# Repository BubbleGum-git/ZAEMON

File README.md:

# BE Capstone Project

**ZAEMON — Dynamically Balanced Wheeled Bipedal Robot**  
[Our Project proposal presentation](https://www.youtube.com/watch?v=3FdDc5E4eX4)

---

## Team Details

| Sr. No. | Name of Student | Roll No. | Branch                  | Email ID |
| ------- | --------------- | -------- | ----------------------- | -------- |
| 1       |Suraj Kumbhar|9| Automation and Robotics |2023.suraj.kumbhar@ves.ac.in|
| 2       |Baljeet Singh Labana|10| Automation and Robotics |2023.baljeet.labana@ves.ac.in|
| 3       |Aayush Maluste|13| Automation and Robotics |2023.aayush.maulste@ves.ac.in|
| 4       |Jai Bagul|35| Automation and Robotics |2023.jai.bagul@ves.ac.in|

---

## Guide Details

**Project Guide:** 
Madhumati Khuspe  
**Department:** 
Automation and Robotics  
**Institute:** 
Vivekanand Education Society's Institute of Technology, Mumbai

---

## Problem Statement

Conventional wheeled robots provide efficient locomotion but are generally limited to stable configurations and relatively simple movements. Legged robots offer greater mobility and dynamic capabilities but require more complex mechanical structures and control systems.

The aim of ZAEMON is to design and develop an open source dynamically balanced wheeled bipedal robot platform and hardware capable of maintaining balance, performing controlled wheeled locomotion, and executing dynamic movements such as jumping through real-time sensing, trajectory planning, dynamic modelling, and feedback control.

---

## Abstract

ZAEMON is a dynamically balanced wheeled bipedal robot developed to combine the efficiency of wheeled locomotion with the dynamic capabilities of a legged robotic system. Due to its variable center of mass, the robot behaves similarly to an inverted pendulum and requires continuous active stabilization to remain balanced.

The project focuses on the mechanical design, kinematic and dynamic modelling and real-time control of the robot.

An IMU provides real-time orientation feedback for estimating the robot's tilt and motion. PID control is used for balance stabilization and normal locomotion, while computed torque control is investigated for dynamic movements such as jumping.

The project aims to develop and experimentally validate a compact robotic platform capable of dynamic balancing, controlled locomotion, and agile movement.

---

## Objectives

1. To design and develop a dynamically balanced wheeled bipedal robot.
2. To study the kinematics and dynamics of the robotic system.
3. To implement inverse dynamics.
4. To develop smooth joint-space and Cartesian-space trajectories.
5. To implement real-time balance control using IMU feedback.
6. To implement PID-based stabilization for balancing and locomotion.
7. To investigate computed torque control for dynamic movements.
8. To integrate the mechanical, electrical, and software systems.
9. To experimentally test and validate the developed system.

---

## Existing System

Conventional wheeled robots provide efficient and relatively simple locomotion but have limited ability to dynamically change their body configuration or perform agile movements.

Legged robots provide greater mobility and dynamic capabilities but typically involve:

* Higher mechanical complexity
* Multiple actuators
* Complex control algorithms
* Higher computational requirements
* Increased power consumption

ZAEMON explores a hybrid approach that combines efficient wheeled locomotion with actively controlled leg joints.

---

## Current Hardware

The hardware architecture consists of:

* Microcontroller ESP32 S3
* IMU MPU6050
* Motors and actuators - BLDC Gimbal Motor
* Motor drivers - DRV8313 FOC driver
* Encoders - AS5600 Magnetic encoder
* Power supply and battery system
* Voltage regulation and power distribution circuitry

Detailed hardware specifications will be documented as the design is finalized.

---

## Design Files

Design files are maintained in the following directories:

```text
hardware/
├── CAD/
```

---

## Circuit Diagram

The circuit diagram will be added as the electronics architecture is finalized.

---

### Control Algorithm

1. Initialize the controller and sensors.
2. Read IMU and encoder measurements.
3. Estimate the current robot state.
4. Calculate the error from the desired state.
5. Generate the desired trajectory.
6. Calculate the required control action.
7. Generate motor commands.
8. Apply commands to the actuators.
9. Read the updated sensor state.
10. Repeat the control loop in real time.

---

## Implementation Details

### Hardware Implementation

The hardware implementation consists of the mechanical structure, actuators, motor drivers, embedded controller, IMU, encoders, and power system.

The mechanical structure is designed to provide the required degrees of freedom for balancing, locomotion, and dynamic movement.

ime feedback

---

## Repository Structure

```text
ZAEMON/
│
├── README.md
│
├── docs/
│   ├── progress/
│   ├── design/
│   └── reports/
│
├── hardware/
│   ├── CAD/
│   ├── PCB/
│   ├── schematics/
│   └── BOM/
│
├── software/
│   ├── firmware/
│   ├── control/
│   ├── simulation/
│   └── tools/
│
├── images/
│
└── reference/
```

---

## How to Run

Build, firmware upload, and simulation instructions will be added as the software and hardware platforms are finalized.

---

## Applications

Potential applications of ZAEMON include:

1. Research in dynamically balanced robotics.
2. Agile robotic locomotion research.
3. Balance and control system research.
4. Dynamic trajectory and model-based control research.
5. Educational and experimental robotics.

---

## Advantages

1. Combines wheeled locomotion with bipedal movement.
2. Enables active dynamic balancing.
3. Supports model-based motion planning and control.
4. Provides a platform for studying dynamic robotic movement.
5. Can be extended with advanced control and autonomous capabilities.

---

## Limitations

1. Requires continuous active control for maintaining balance.
2. Dynamic movement requires accurate state estimation and modelling.
3. Mechanical and control complexity is higher than conventional wheeled robots.
4. Actuator and battery performance constrain the robot's capabilities.
5. Initial testing is intended for controlled environments.

---

## Future Scope

Future development may include:

* Autonomous navigation
* Advanced sensor fusion and state estimation
* Adaptive and robust control
* Improved landing and impact control
* More complex dynamic movements
* Real-time optimization of the dynamic model
* Improved mechanical and actuator design

---

## License

This project is developed as part of the BE Capstone Project at VESIT, Mumbai.

**For academic and research purposes.**

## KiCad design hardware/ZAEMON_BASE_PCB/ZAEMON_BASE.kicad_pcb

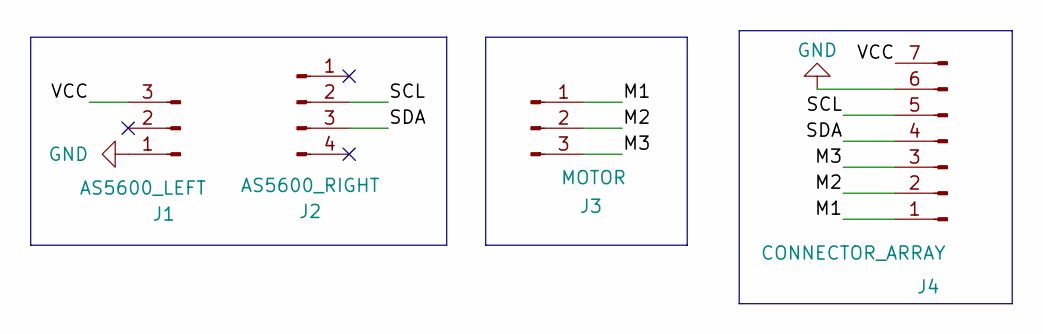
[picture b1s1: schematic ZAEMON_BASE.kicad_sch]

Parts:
J1: AS5600_LEFT; PinHeader_1x03_P2.54mm_Vertical
J2: AS5600_RIGHT; PinHeader_1x04_P2.54mm_Vertical
J3: MOTOR; PinHeader_1x03_P2.54mm_Vertical
J4: CONNECTOR_ARRAY; PinHeader_1x07_P2.54mm_Vertical

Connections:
/M1: J3.1, J4.1
/M2: J3.2, J4.2
/M3: J3.3, J4.3
/SCL: J2.2, J4.5
/SDA: J2.3, J4.4
/VCC: J1.3, J4.7
GND: J1.1, J4.6

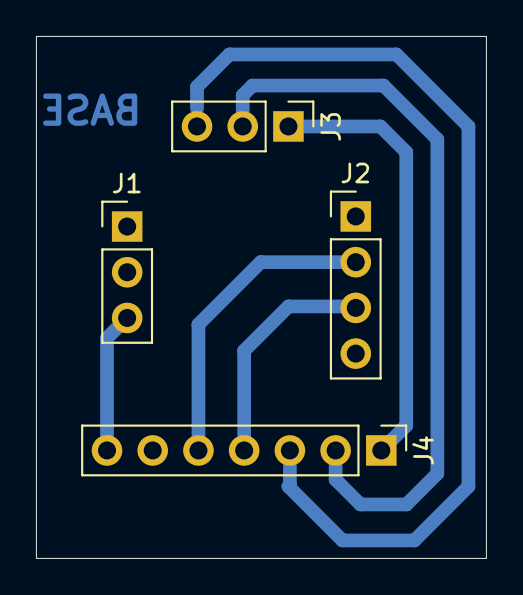
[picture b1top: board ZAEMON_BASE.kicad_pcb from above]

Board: 2 copper layers, 25.0 x 29.0 mm, 4 parts (0 on the bottom side), 7 nets.

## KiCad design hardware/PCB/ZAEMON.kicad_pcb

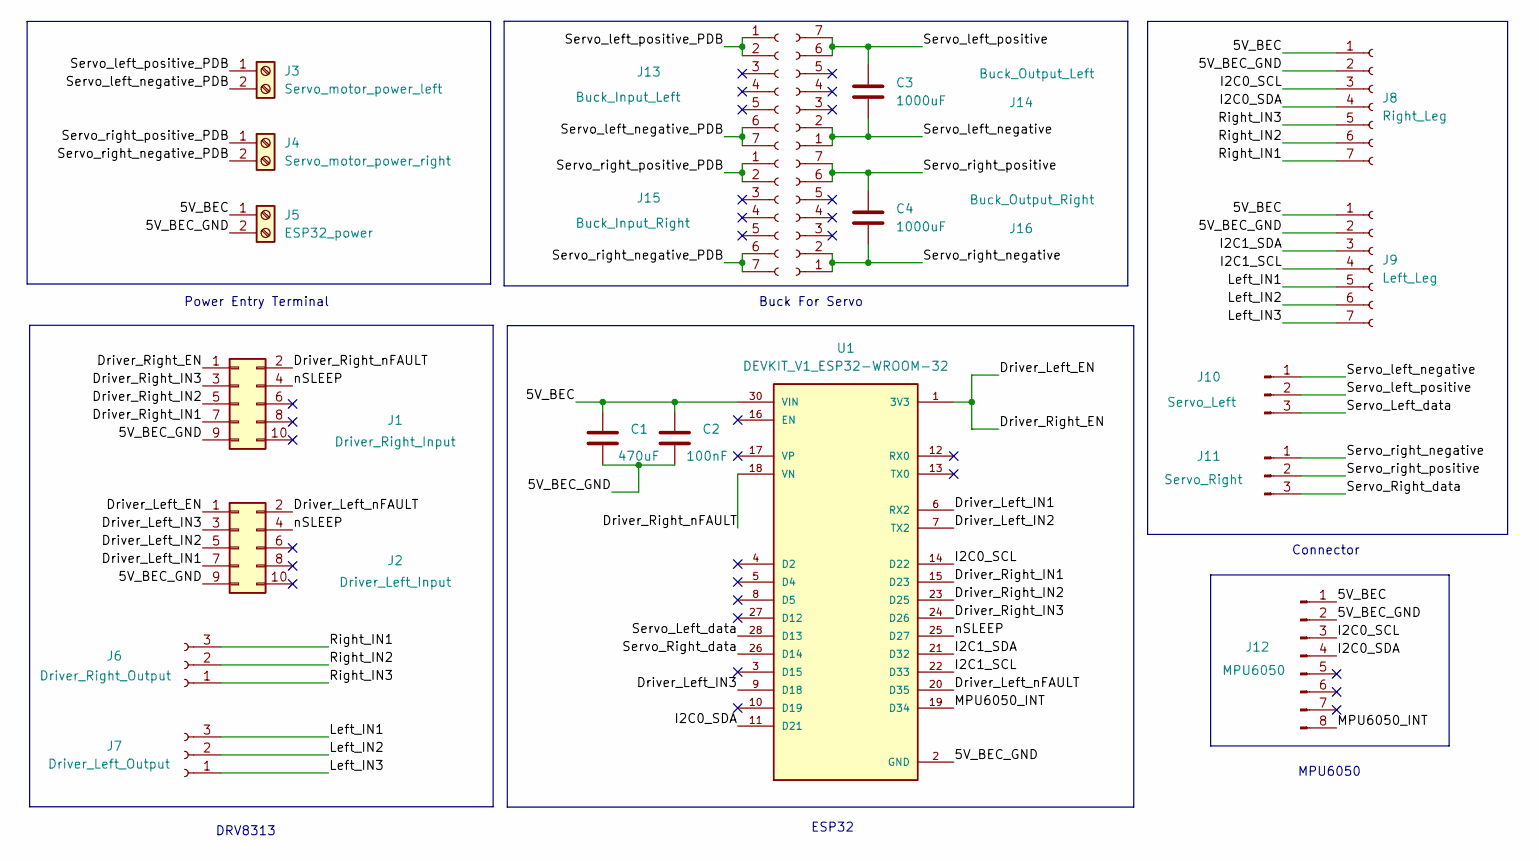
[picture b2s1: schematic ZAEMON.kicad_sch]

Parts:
C1: 470uF; CP_Radial_D10.0mm_P5.00mm
C2: 100nF; C_Disc_D5.0mm_W2.5mm_P5.00mm
C3, C4: 1000uF; CP_Radial_D10.0mm_P5.00mm
J1: Driver_Right_Input; PinHeader_2x05_P2.54mm_Vertical
J2: Driver_Left_Input; PinHeader_2x05_P2.54mm_Vertical
J3: Servo_motor_power_left; TerminalBlock_Phoenix_MKDS-1,5-2-5.08_1x02_P5.08mm_Horizont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
J4: Servo_motor_power_right; TerminalBlock_Phoenix_MKDS-1,5-2-5.08_1x02_P5.08mm_Horizont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
J5: ESP32_power; TerminalBlock_Phoenix_MKDS-1,5-2-5.08_1x02_P5.08mm_Horizont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
J6: Driver_Right_Output; PinHeader_1x03_P2.54mm_Vertical
J7: Driver_Left_Output; PinHeader_1x03_P2.54mm_Vertical
J8: Right_Leg; PinHeader_1x07_P2.54mm_Vertical
J9: Left_Leg; PinHeader_1x07_P2.54mm_Vertical
J10: Servo_Left; PinHeader_1x03_P2.54mm_Vertical
J11: Servo_Right; PinHeader_1x03_P2.54mm_Vertical
J12: MPU6050; PinHeader_1x08_P2.54mm_Vertical
J13: Buck_Input_Left; PinHeader_1x07_P2.54mm_Vertical
J14: Buck_Output_Left; PinHeader_1x07_P2.54mm_Vertical
J15: Buck_Input_Right; PinHeader_1x07_P2.54mm_Vertical
J16: Buck_Output_Right; PinHeader_1x07_P2.54mm_Vertical
U1: DEVKIT_V1_ESP32-WROOM-32; MODULE_DEVKIT_V1_ESP32-WROOM-32

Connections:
/5V_BEC: C1.1, C2.1, J5.1, J8.1, J9.1, J12.1, U1.30 (VIN)
/Driver_Left_EN: J1.1, J2.1, U1.1 (3V3)
/Driver_Left_IN1: J2.7, U1.6 (RX2)
/Driver_Left_IN2: J2.5, U1.7 (TX2)
/Driver_Left_IN3: J2.3, U1.9 (D18)
/Driver_Left_nFAULT: J2.2, U1.20 (D35)
/Driver_Right_IN1: J1.7, U1.15 (D23)
/Driver_Right_IN2: J1.5, U1.23 (D25)
/Driver_Right_IN3: J1.3, U1.24 (D26)
/Driver_Right_nFAULT: J1.2, U1.18 (VN)
/I2C0_SCL: J8.3, J12.3, U1.14 (D22)
/I2C0_SDA: J8.4, J12.4, U1.11 (D21)
/I2C1_SCL: J9.4, U1.22 (D33)
/I2C1_SDA: J9.3, U1.21 (D32)
/Left_IN1: J7.3, J9.5
/Left_IN2: J7.2, J9.6
/Left_IN3: J7.1, J9.7
/MPU6050_INT: J12.8, U1.19 (D34)
/Right_IN1: J6.3, J8.7
/Right_IN2: J6.2, J8.6
/Right_IN3: J6.1, J8.5
/Servo_Left_data: J10.3, U1.28 (D13)
/Servo_Right_data: J11.3, U1.26 (D14)
/Servo_left_negative: C3.2, J10.1, J14.1, J14.2
/Servo_left_negative_PDB: J3.2, J13.6, J13.7
/Servo_left_positive: C3.1, J10.2, J14.6, J14.7
/Servo_left_positive_PDB: J3.1, J13.1, J13.2
/Servo_right_negative: C4.2, J11.1, J16.1, J16.2
/Servo_right_negative_PDB: J4.2, J15.6, J15.7
/Servo_right_positive: C4.1, J11.2, J16.6, J16.7
/Servo_right_positive_PDB: J4.1, J15.1, J15.2
/nSLEEP: J1.4, J2.4, U1.25 (D27)
GND: C1.2, C2.2, J1.9, J2.9, J5.2, J8.2, J9.2, J12.2, U1.2 (GND), U1.29 (GND)

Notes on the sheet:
Buck For Servo
Connector
MPU6050
ESP32
Power Entry Terminal
DRV8313

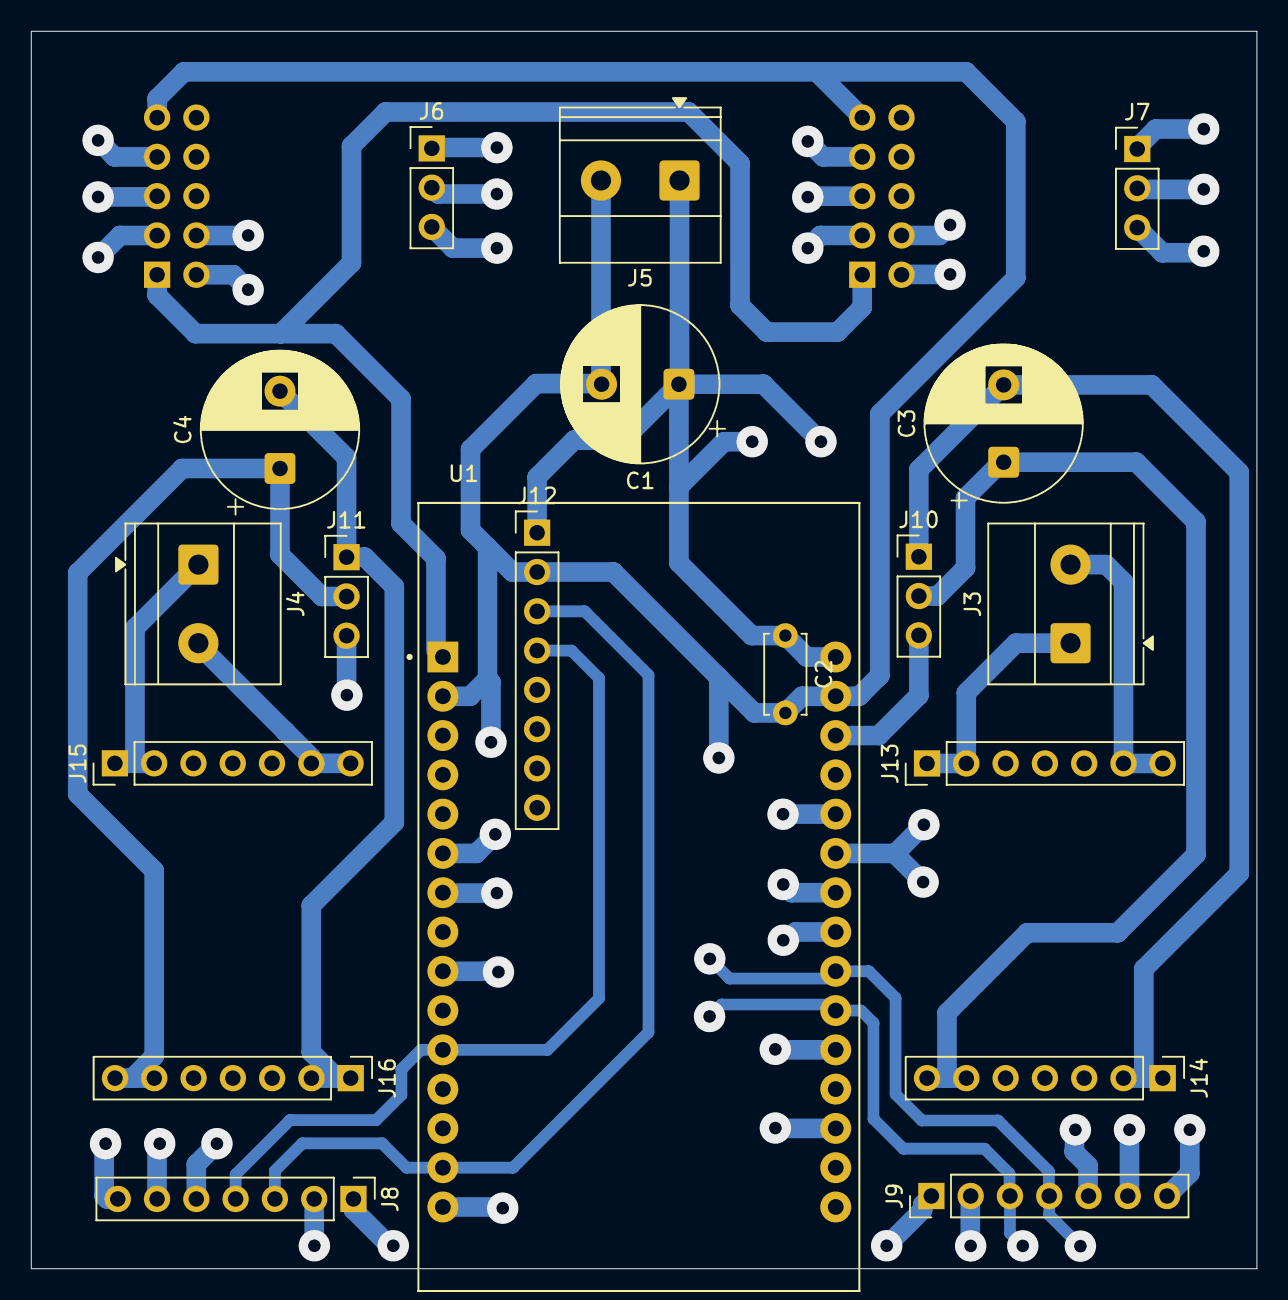
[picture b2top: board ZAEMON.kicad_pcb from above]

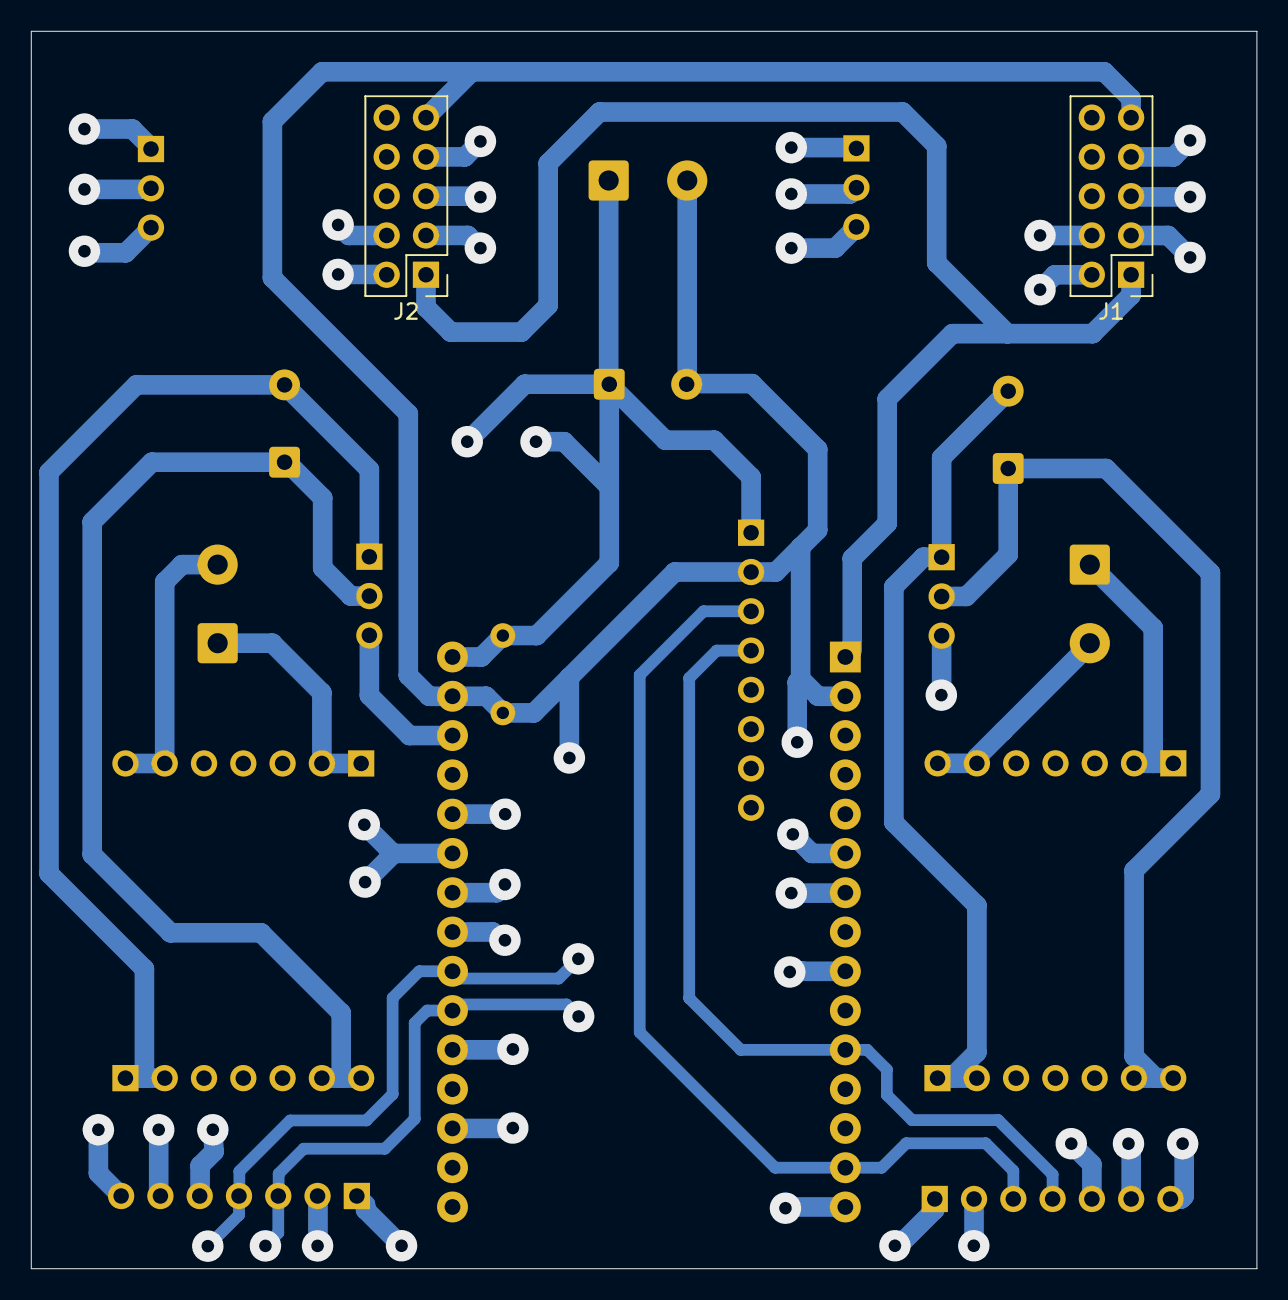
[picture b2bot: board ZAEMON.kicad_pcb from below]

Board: 2 copper layers, 79.2 x 80.0 mm, 21 parts (2 on the bottom side), 33 nets.
